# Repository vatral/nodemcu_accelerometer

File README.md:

# NodeMCU Amica Accelerometer

NodeMCU accelerometer board. This is a trivial test project.

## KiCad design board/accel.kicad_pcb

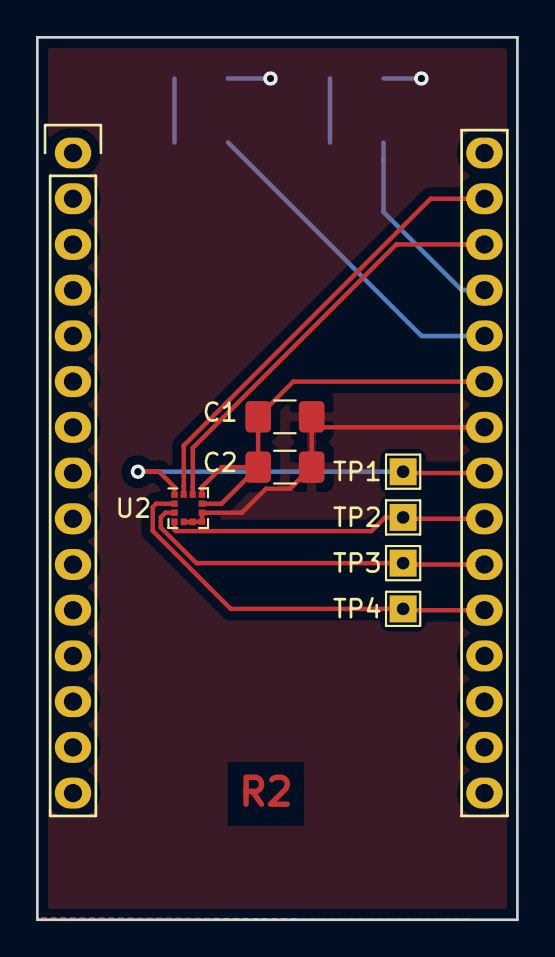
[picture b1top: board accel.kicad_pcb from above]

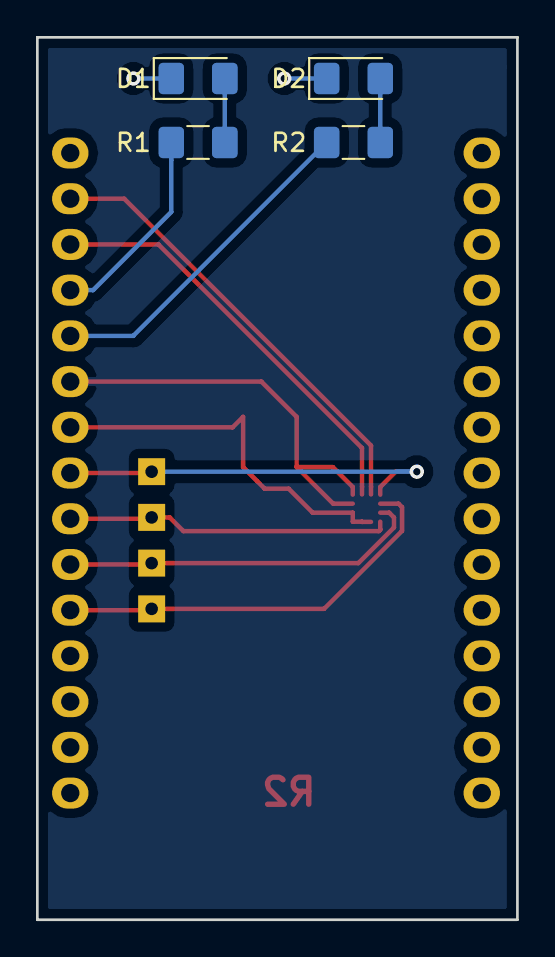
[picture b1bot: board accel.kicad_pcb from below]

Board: 2 copper layers, 26.7 x 49.0 mm, 12 parts (4 on the bottom side), 12 nets.

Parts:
C1: 10uF; C_1206_3216Metric_Pad1.42x1.75mm_HandSolder
C2: 10nF; C_1206_3216Metric_Pad1.42x1.75mm_HandSolder
D1, D2: LED; LED_1206_3216Metric_Pad1.42x1.75mm_HandSolder
R1, R2: R; R_1206_3216Metric_Pad1.42x1.75mm_HandSolder
TP1, TP2, TP3, TP4: TestPoint; TestPoint_THTPad_1.5x1.5mm_Drill0.7mm
U1: NodeMCU_Amica_R2
U2: LIS2HH12; LGA-12_2x2mm_P0.5mm

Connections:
+3V3: C1.2, C2.2, U1.25, U2.9, U2.10
/INT1: U1.29, U2.12
/INT2: U1.28, U2.11
/SPI_CLK: TP1.1, U1.23, U2.1
/SPI_CS: TP4.1, U1.20, U2.2
/SPI_MISO: TP3.1, U1.21, U2.3
/SPI_MOSI: TP2.1, U1.22, U2.4
GND: C1.1, C2.1, D1.1, D2.1, U1.24, U2.5, U2.6, U2.7, U2.8
unnamed: D1.2, R1.2
unnamed: D2.2, R2.1
unnamed: R1.1, U1.27
unnamed: R2.2, U1.26

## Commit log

2018-09-16 Initial version
2018-09-22 Mark board as R2 to distinguish from previously manufactured one.
